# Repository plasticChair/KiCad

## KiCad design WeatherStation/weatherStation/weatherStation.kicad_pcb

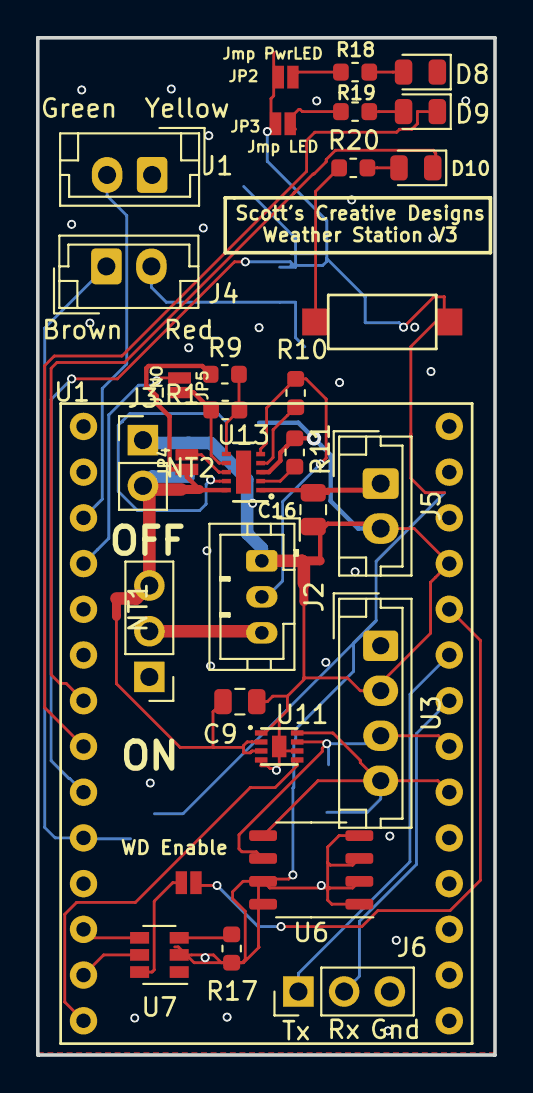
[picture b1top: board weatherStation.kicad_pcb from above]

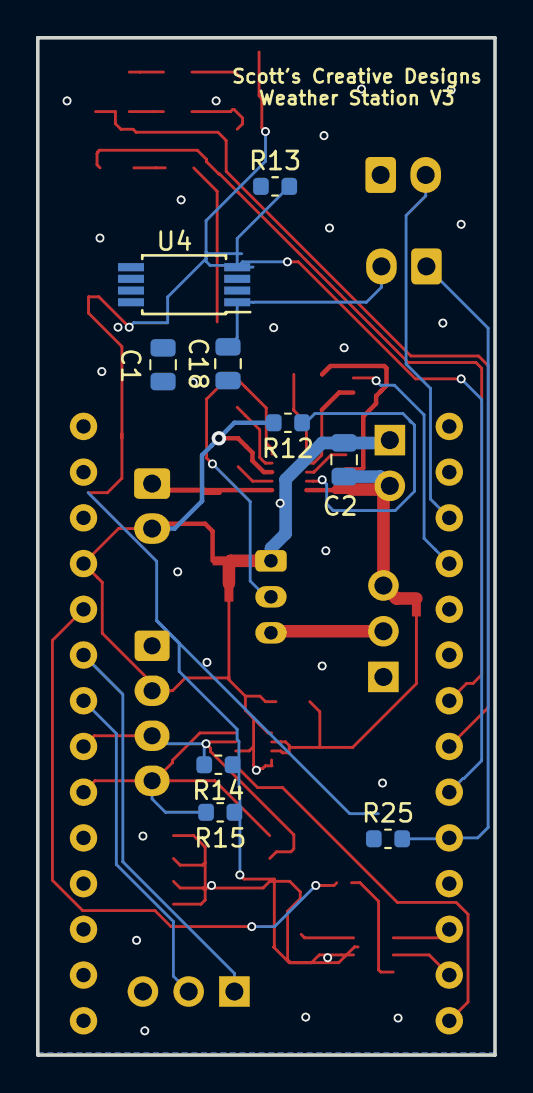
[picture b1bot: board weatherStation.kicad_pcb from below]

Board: 2 copper layers, 25.4 x 56.5 mm, 45 parts (9 on the bottom side), 37 nets.

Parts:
C1, C18: 100nF; C_0805_2012Metric
C2, C16: 1uF; C_0805_2012Metric
C9: 0.1uF; C_0805_2012Metric
D8: 3V3 OK; LED_0805_2012Metric
D9, D10: GPLED; LED_0805_2012Metric
J1, J4, J5: Conn_01x02; JST_EH_B02B-EH-A_1x02_P2.50mm_Vertical
J2: Conn_01x03; JST_PH_B3B-PH-K_1x03_P2.00mm_Vertical
J3: Conn_01x02_Female; PinHeader_1x02_P2.54mm_Vertical
J6: Conn_01x03_Female; PinHeader_1x03_P2.54mm_Vertical
JP1: Jmp_NO; SMT-JUMPER_2_NO_NO-SILK
JP2: Jmp PwrLED; SMT-JUMPER_2_NO_NO-SILK
JP3: Jmp LED; SMT-JUMPER_2_NO_NO-SILK
JP4, JP5: J_NO; SMT-JUMPER_2_NO_NO-SILK
NT1, NT2, NT3, NT4: Net-Tie_2; NetTie-2_SMD_Pad0.5mm
R1, R13, R25: 10k; R_0603_1608Metric
R9: 100k; R_0603_1608Metric
R10: RT; R_0603_1608Metric
R11: 750; R_0603_1608Metric
R12: 330; R_0603_1608Metric
R14, R15: 5k; R_0603_1608Metric
R17: 33k; R_0603_1608Metric
R18, R19, R20: 300; R_0603_1608Metric
SW2: SW_SPDT; PinHeader_1x03_P2.54mm_Vertical
SW3: LED_Push; Tact_SMD_Switch
U1: MKRGSM1400
U3: BME280; JST_EH_B04B-EH-A_1x04_P2.50mm_Vertical
U4: FDW254p; TSSOP-8_4.4x3mm_P0.65mm
U6: MB85RC64; SSOP-8_3.9x5.05mm_P1.27mm
U7: TPL5010; SOT-23-6
U11: MAX17048; TQFN-8_2x2x0.75
U13: BQ24210; WSON-10-1EP_2x3mm_P0.5mm_EP0.84x2.4mm

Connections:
3V3: C1.2, JP2.2, JP3.1, R13.1, R14.1, R15.1, R25.1, SW3.1, U1.26, U3.1, U4.2, U4.3, U6.8, U7.1
/ANE_Pulse: J1.2, U1.3
/ANE_Tx: J4.1, R25.2, U1.10
/ANE_Vcc: C18.2, J4.2, U4.1
/ANE_Vcc_EN: R13.2, U1.9, U4.4
/DONE: U1.12, U7.4
/GPLED1: D9.1, U1.8
/GPLED2: D10.1, U1.7
/RESET: JP1.2, U1.24
/Sheet5C1E5C91/Batt+: C2.1, J3.2, NT1.1, NT2.1, SW2.3
/Sheet5C1E5C91/BattMon+: C9.2, NT1.2, U11.2, U11.3
/Sheet5C1E5C91/Batt_Chrg+: JP4.1, NT2.2, R9.1, U13.10
/Sheet5C1E5C91/Batt_int: J2.3, SW2.2
/Sheet5C1E5C91/NTC: J2.2, R10.2, U13.5
/Sheet5C1E5C91/Solar+: C16.1, J5.1, U13.1
/WAKE: U1.13, U7.5
BATT_ALRT: U1.14, U11.5
CHRG_EN: JP5.1, U1.4
GND: C1.1, C2.2, C9.1, C16.2, C18.1, D8.1, J1.1, J2.1, J3.1, J5.2, J6.3, NT3.1, NT3.2, NT4.1, NT4.2, R11.2, R12.2, R17.1, U1.25, U3.2, U6.1, U6.2, U6.3, U6.4, U6.7, U7.2, U11.1, U11.4, U11.6, U11.9, U13.3
I2C_SCL: R14.2, U1.21, U3.3, U6.6, U11.7
I2C_SDA: R15.2, U1.20, U3.4, U6.5, U11.8
unnamed: D8.2, R18.1
unnamed: D9.2, R19.2
unnamed: D10.2, R20.1
unnamed: J6.1, U1.23
unnamed: J6.2, U1.22
unnamed: JP1.1, U7.6
unnamed: JP2.1, R18.2
unnamed: JP3.2, R19.1
unnamed: JP4.2, U13.8
unnamed: JP5.2, R1.2, U13.7
unnamed: R1.1, R9.2, U13.6
unnamed: R10.1, U13.4
unnamed: R11.1, U13.2
unnamed: R12.1, U13.9
unnamed: R17.2, U7.3
unnamed: R20.2, SW3.2

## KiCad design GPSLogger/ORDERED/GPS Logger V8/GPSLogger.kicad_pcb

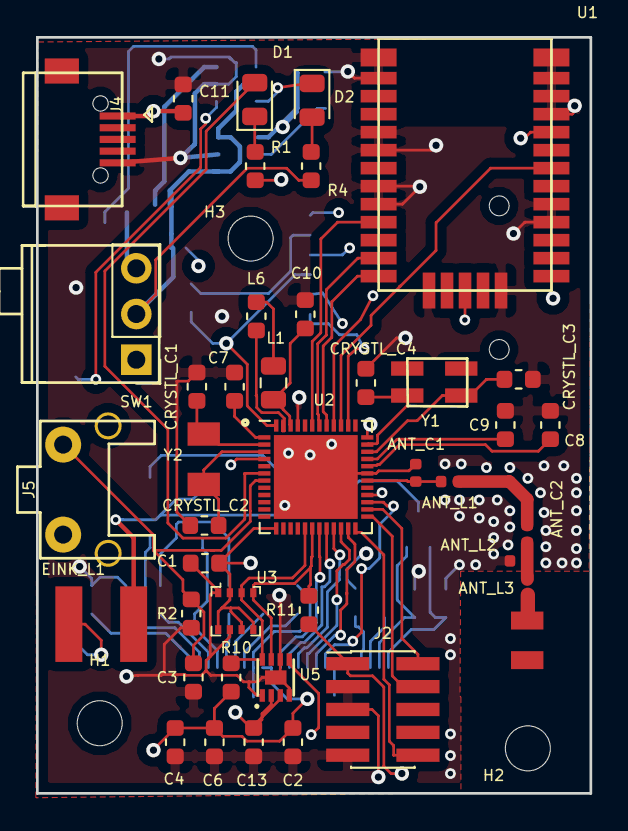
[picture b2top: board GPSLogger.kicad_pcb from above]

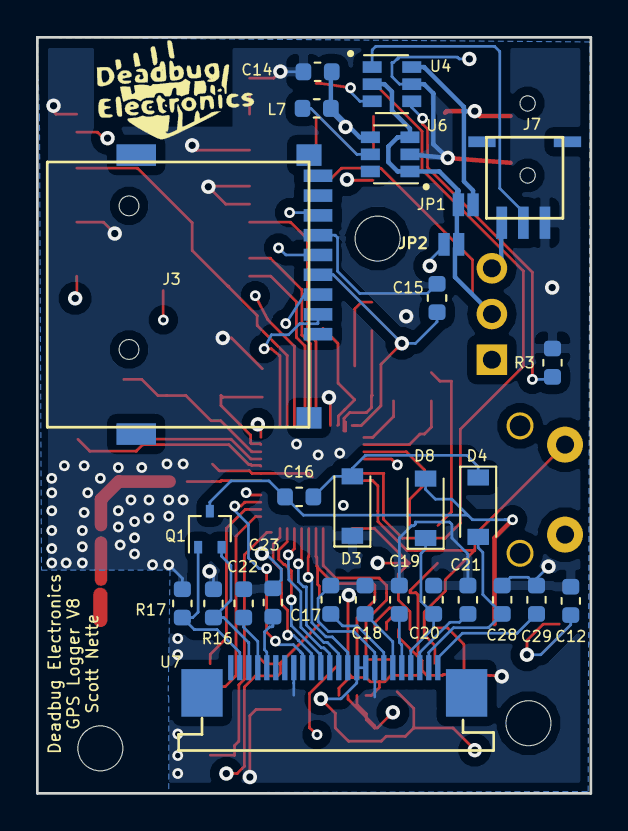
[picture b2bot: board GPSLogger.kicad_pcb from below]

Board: 4 copper layers, 30.8 x 42.0 mm, 72 parts (28 on the bottom side), 61 nets.

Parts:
ANT1: 2450AT18B100E
ANT_C1: 0.8pF; C_0402_1005Metric
ANT_C2: 1.2pF; C_0402_1005Metric
ANT_L1: 3.9nH; L_0402_1005Metric
ANT_L2: 2.7nH; L_0402_1005Metric
ANT_L3: 3.3nH; L_0402_1005Metric
C1: 82n; C_0603_1608Metric
C2: 2.2u; C_0603_1608Metric
C3, C11: 100nF; C_0603_1608Metric
C4, C6: 0.1u; C_0603_1608Metric
C7, C12, C16: 100n; C_0603_1608Metric
C8: NC; C_0603_1608Metric
C9: 100p; C_0603_1608Metric
C10, C13, C17, C18, C19, C20, C21, C22, C23, C28, C29: 1u; C_0603_1608Metric
C14: C; C_0603_1608Metric
C15: 4.7u; C_0603_1608Metric
CRYSTL_C1, CRYSTL_C2, CRYSTL_C3, CRYSTL_C4: 12p; C_0603_1608Metric
D1: LED_B; LED_0805_2012Metric
D2: LED; LED_0805_2012Metric
D3, D4, D8: MBR0530; D_SOD-123
EINK_L1: 68uH; SRN5040TA-680K
H1, H2, H3: MountingHole; MountingHole_2.5mm
J2: Conn_ARM_JTAG_SWD_10; PinHeader_2x05_P1.27mm_Vertical_SMD
J3: Micro_SD_Card; microSD_ebay
J4: USB_B_Micro; USB_Micro-B_Ebay
J5: BTN1; ebay_RA_Mom_switch
J7: Batt_Connector; molex_78172-0003
JP1, JP2: Jumper_NO_Small; SMT-JUMPER_2_NO_NO-SILK
L1: 10nH; L_0805_2012Metric
L6: 15uH; L_0603_1608Metric
L7: INDUCTOR; L_0603_1608Metric
Q1: Q_NMOS_GSD; SOT-323_SC-70
R1: 5.6; R_0603_1608Metric
R2, R17: 10k; R_0603_1608Metric
R3: 1k; R_0603_1608Metric
R4: 330; R_0603_1608Metric
R10, R11: R; R_0603_1608Metric
R16: 0.47; R_0603_1608Metric
SW1: Switch_SW_SPDT; Slide_Switch_RA_09.10290.01
U1: CAM_M8Q; CAM-M8Q
U2: nRF52832-QFxx; QFN-48-1EP_6x6mm_P0.4mm_EP4.66x4.66mm
U3: BME280; Pressure_Sensor_LGA-8_2.5x2.5mm_BME280
U4: BQ21040; SOT-23-6
U5: MAX17048; TQFN-8_2x2x0.75
U6: LM3671; SOT-23-6
U7: 24pin_flex_waveshare; 24pin_Flex_bottom
Y1: 32MHz; ECS-320-12-33Q
Y2: 32.768kHz; TFE322P32K7680R

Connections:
/BatteryManagement/Batt+: JP1.2, JP2.2, R4.1, SW1.2, U4.2, U6.1, U6.3
/BatteryManagement/BattInt: J7.3, SW1.3
/BatteryManagement/NTC: J7.2, U4.1
/DEC1: C7.1, U2.1
/DEC2: C8.1, U2.32
/DEC3: C9.1, U2.33
/DEC4: C10.1, L1.1, U2.46
/EINK/GDR: Q1.1, R17.1, U7.2
/EINK/PREVGH: C20.1, D8.1, U7.21
/EINK/PREVGL: C28.1, D4.2, U7.23
/EINK/RESE: Q1.2, R16.1, U7.3
/EINK/VCOM: C29.1, U7.24
/EINK/VDD: C17.1, U7.18
/EINK/VPP: C18.1, U7.19
/EINK/VSH: C19.1, U7.20
/EINK/VSL: C21.1, U7.22
/EINK_BUSY: U2.27, U7.9
/EINK_DC: U2.22, U7.11
/EINK_RST: U2.23, U7.10
/GPS_ExtInt: U1.7, U2.39
/GPS_Reset: U1.23, U2.43
/GPS_TimePulse: U1.29, U2.40
/RESET: J2.10, U2.24
/SD_CS: J3.2, U2.38
/SPI_CLK: J3.5, U2.20, U7.13
/SPI_EINK_CS: U2.21, U7.12
/SPI_MISO: J3.7, U2.28
/SPI_MOSI: J3.3, U2.19, U7.14
/SWDCLK: J2.4, U2.25
/SWDIO: J2.2, U2.26
ALRT: U2.4, U5.5
BattPwr: C13.1, JP2.1, U5.2, U5.3
BattRtn: ANT_C1.2, ANT_L2.1, C1.2, C2.2, C3.2, C4.1, C6.1, C7.2, C8.2, C9.2, C10.2, C11.1, C12.2, C13.2, C14.2, C15.2, C17.2, C18.2, C19.2, C20.2, C21.2, C22.2, C23.2, C28.2, C29.2, CRYSTL_C1.2, CRYSTL_C2.2, CRYSTL_C3.1, CRYSTL_C4.1, D3.1, J2.3, J2.5, J2.9, J3.6, J4.5, J7.1, R2.2, R3.1, R16.2, R17.2, U1.4, U1.5, U1.10, U1.11, U1.12, U1.13, U1.14, U1.15, U1.18, U1.19, U1.21, U1.22, U1.27, U1.31, U2.31, U2.45, U2.49, U3.1, U3.7, U4.5, U5.1, U5.4, U5.6, U5.9, U6.2, U7.8, U7.17
Fun_Btn_1_P23: C3.1, J5.1, R2.1, U2.7
LED1_P2: D1.2, U2.6
unnamed: ANT1.1, ANT_L3.1
unnamed: ANT_C1.1, ANT_L1.2, U2.30
unnamed: ANT_C2.1, ANT_L1.1
unnamed: ANT_C2.2, ANT_L2.2, ANT_L3.2
unnamed: C16.1, D3.2, D4.1
unnamed: C16.2, D8.2, EINK_L1.2, Q1.3
unnamed: C22.1, U7.4
unnamed: C23.1, U7.5
unnamed: CRYSTL_C1.1, U2.2, Y2.1
unnamed: CRYSTL_C2.1, U2.3, Y2.2
unnamed: CRYSTL_C3.2, U2.34, Y1.1
unnamed: CRYSTL_C4.2, U2.35, Y1.2
unnamed: D1.1, R1.1
unnamed: D2.1, U4.3
unnamed: D2.2, R4.2
unnamed: L1.2, L6.1
unnamed: L6.2, U2.47
unnamed: L7.1, U6.5
unnamed: R3.2, U4.4
unnamed: U1.16, U1.17
SCL: R11.2, U2.18, U3.4, U5.7
SDA: R10.2, U2.17, U3.3, U5.8
UART_RX: U1.25, U2.42
UART_TX: U1.26, U2.41
USB_PWR: C11.2, J4.1, JP1.1, U4.6
Vdd: C1.1, C2.1, C4.2, C6.2, C12.1, C14.1, C15.1, EINK_L1.1, J2.1, J3.4, J5.2, L7.2, R1.2, R10.1, R11.1, U1.1, U1.9, U2.13, U2.36, U2.48, U3.2, U3.5, U3.6, U3.8, U6.4, U7.15, U7.16

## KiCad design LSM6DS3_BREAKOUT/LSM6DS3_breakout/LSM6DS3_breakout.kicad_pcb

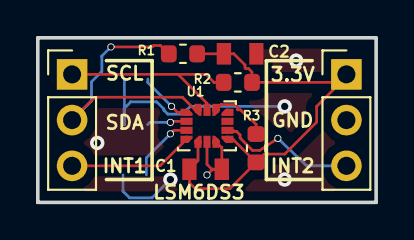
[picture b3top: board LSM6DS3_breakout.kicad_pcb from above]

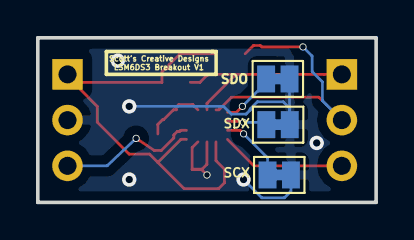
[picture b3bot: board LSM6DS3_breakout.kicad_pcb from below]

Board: 2 copper layers, 18.8 x 9.1 mm, 11 parts (3 on the bottom side), 10 nets.

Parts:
C1, C2: C_Small; 0805
J1, J2: Conn_01x03_Male; PinHeader_1x03_P2.54mm_Vertical
R1, R2: 5.1k; R_0603_1608Metric
R3: 10k; R_0603_1608Metric
SCX: J_NC; SolderJumper-2_P1.3mm_Bridged_Pad1.0x1.5mm
SDO: J_NC; SolderJumper-2_P1.3mm_Bridged_Pad1.0x1.5mm
SDX: J_NC; SolderJumper-2_P1.3mm_Bridged_Pad1.0x1.5mm
U1: LSM6DS3; LGA-14_3x2.5mm_P0.5mm_LayoutBorder3x4y

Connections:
+3V3: C1.2, C2.1, J2.1, R1.2, R2.2, R3.2, U1.5, U1.8
/CS: R3.1, U1.12
/INT1: J1.3, U1.4
/INT2: J2.3, U1.9
/SCL: J1.1, R2.1, U1.13
/SCX: SCX.1, U1.3
/SDA: J1.2, R1.1, U1.14
/SDO: SDO.1, U1.1
/SDX: SDX.1, U1.2
GND: C1.1, C2.2, J2.2, SCX.2, SDO.2, SDX.2, U1.6, U1.7

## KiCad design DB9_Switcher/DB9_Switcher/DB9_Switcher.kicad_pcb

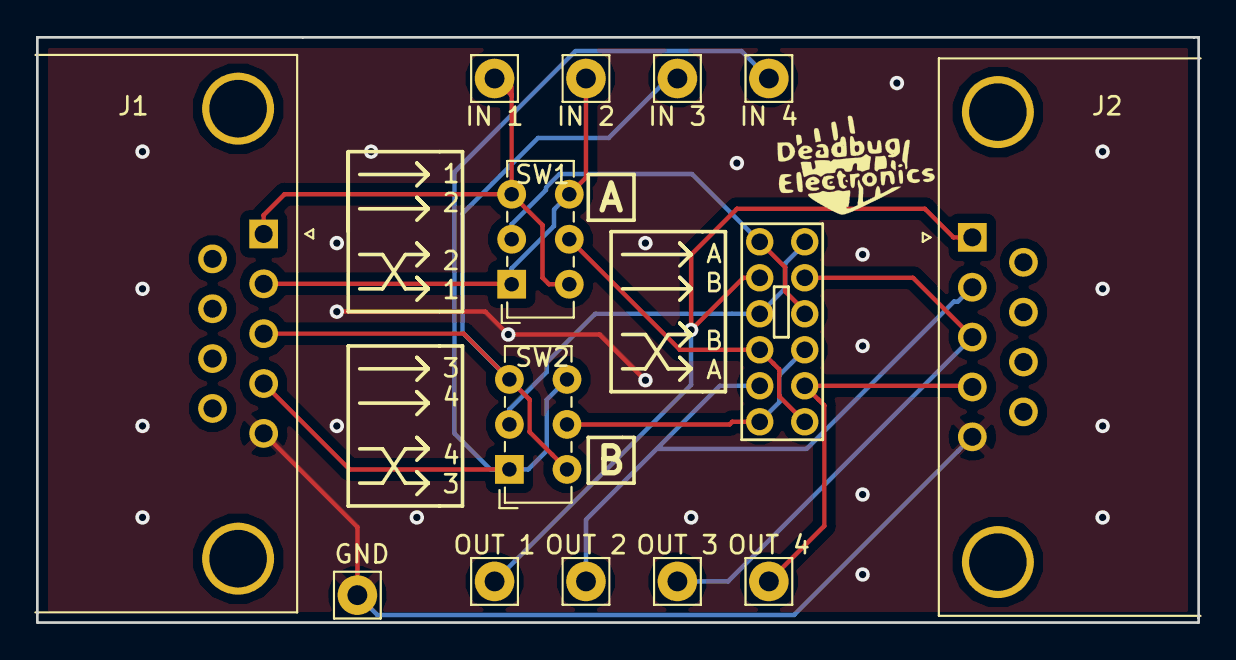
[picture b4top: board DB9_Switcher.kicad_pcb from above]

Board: 2 copper layers, 64.5 x 32.5 mm, 14 parts (0 on the bottom side), 13 nets.

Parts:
GND: GND; Pin_D1.1mm_L8.5mm_W2.5mm_FlatFork
IN 1: IN_1; Pin_D1.1mm_L8.5mm_W2.5mm_FlatFork
IN 2: IN_2; Pin_D1.1mm_L8.5mm_W2.5mm_FlatFork
IN 3: IN_3; Pin_D1.1mm_L8.5mm_W2.5mm_FlatFork
IN 4: IN_4; Pin_D1.1mm_L8.5mm_W2.5mm_FlatFork
J1: DB9_Male; DSUB-9_Male_Horizontal_P2.77x2.84mm_EdgePinOffset9.90mm_Hou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
J2: DB9_Female; DSUB-9_Female_Horizontal_P2.77x2.84mm_EdgePinOffset9.90mm_H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
OUT 1: OUT_1; Pin_D1.1mm_L8.5mm_W2.5mm_FlatFork
OUT 2: OUT_2; Pin_D1.1mm_L8.5mm_W2.5mm_FlatFork
OUT 3: OUT_3; Pin_D1.1mm_L8.5mm_W2.5mm_FlatFork
OUT 4: OUT_4; Pin_D1.1mm_L8.5mm_W2.5mm_FlatFork
SW1, SW2: SW_DPDT_x2; SW_E-Switch_EG1271_DPDT
U1: 4PDTSwitch; MMS42

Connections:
/1: IN 1.1, J1.1, SW1.3, SW1.4
/2: IN 2.1, J1.2, SW1.1, SW1.6
/3: IN 3.1, J1.3, SW2.3, SW2.4
/4: IN 4.1, J1.4, SW2.1, SW2.6
/A_int: SW1.2, U1.1, U1.9
/B_int: SW1.5, U1.4, U1.12
/C_int: SW2.2, U1.3, U1.7
/D_int: SW2.5, U1.6, U1.10
GND: GND.1, J1.5, J2.5
unnamed: J2.1, OUT 1.1, U1.2
unnamed: J2.2, OUT 2.1, U1.5
unnamed: J2.3, OUT 3.1, U1.8
unnamed: J2.4, OUT 4.1, U1.11

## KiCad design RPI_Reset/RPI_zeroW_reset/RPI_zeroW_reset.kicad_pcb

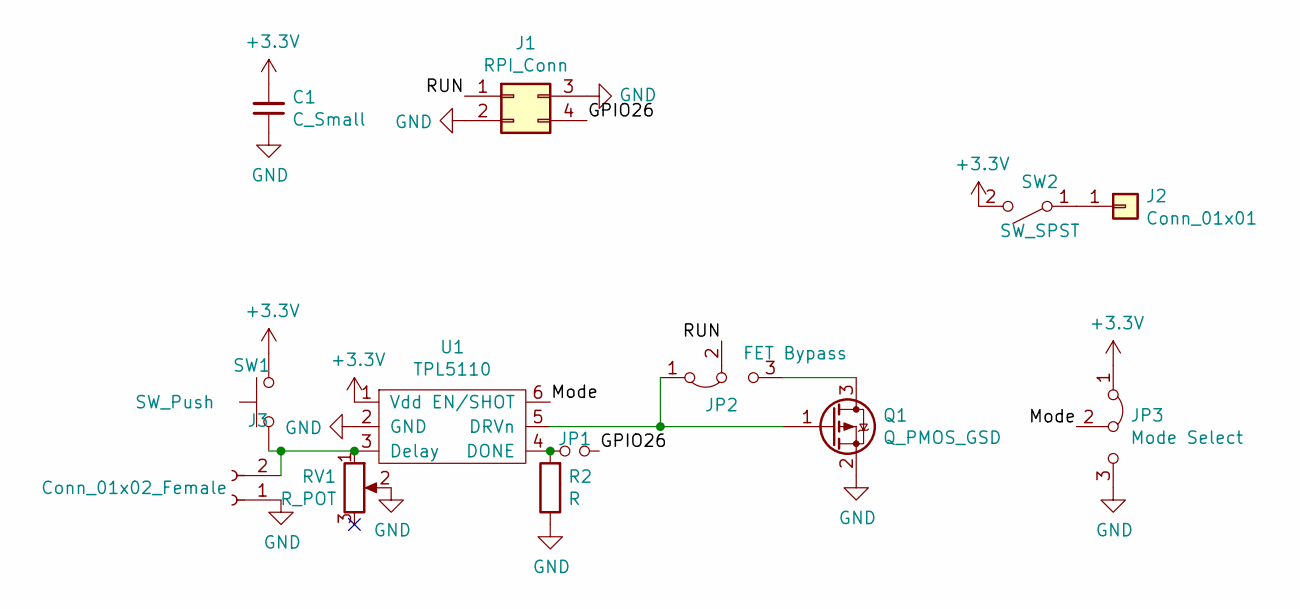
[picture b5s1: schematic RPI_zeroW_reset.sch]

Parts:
C1: C_Small; 0805
J1: RPI_Conn; PinHeader_2x02_P2.54mm_Vertical
J2: Conn_01x01; PinHeader_1x01_P2.54mm_Vertical
J3: Conn_01x02_Female; PinHeader_1x02_P1.27mm_Vertical
JP1: SolderJumper-2_P1.3mm_Open_RoundedPad1.0x1.5mm
JP2: FET Bypass; SolderJumper-3_P1.3mm_Bridged12_RoundedPad1.0x1.5mm
JP3: Mode Select; SolderJumper-3_P1.3mm_Bridged12_RoundedPad1.0x1.5mm
Q1: Q_PMOS_GSD; SOT23
R2: R; R_0805_2012Metric
RV1: R_POT; Bourns_TC33X-2
SW1: SW_Push; Tact_SMD_Switch
SW2: SW_SPST; SWITCH_SPDT_PTH
U1: TPL5110; SOT-23-6

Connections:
+3V3: C1.2, JP3.1 (A), SW1.2, SW2.2 (B), U1.1 (Vdd)
/GPIO26: J1.4, JP1.2
/Mode: JP3.2 (C), U1.6 (EN/SHOT)
/RUN: J1.1, JP2.2 (C)
GND: C1.1, J1.2, J1.3, J3.1, JP3.3 (B), Q1.2 (S), R2.1, RV1.2, U1.2 (GND)
unnamed: J2.1, SW2.1 (A)
unnamed: J3.2, RV1.1, SW1.1, U1.3 (Delay)
unnamed: JP1.1, R2.2, U1.4 (DONE)
unnamed: JP2.1 (A), Q1.1 (G), U1.5 (DRVn)
unnamed: JP2.3 (B), Q1.3 (D)

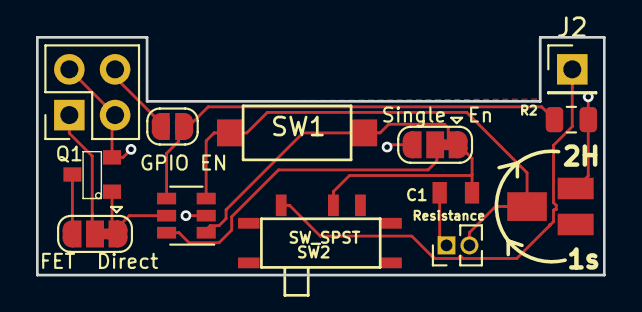
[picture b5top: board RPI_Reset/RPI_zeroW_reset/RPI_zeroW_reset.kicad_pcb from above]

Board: 2 copper layers, 31.5 x 13.2 mm, 13 parts (0 on the bottom side), 10 nets.

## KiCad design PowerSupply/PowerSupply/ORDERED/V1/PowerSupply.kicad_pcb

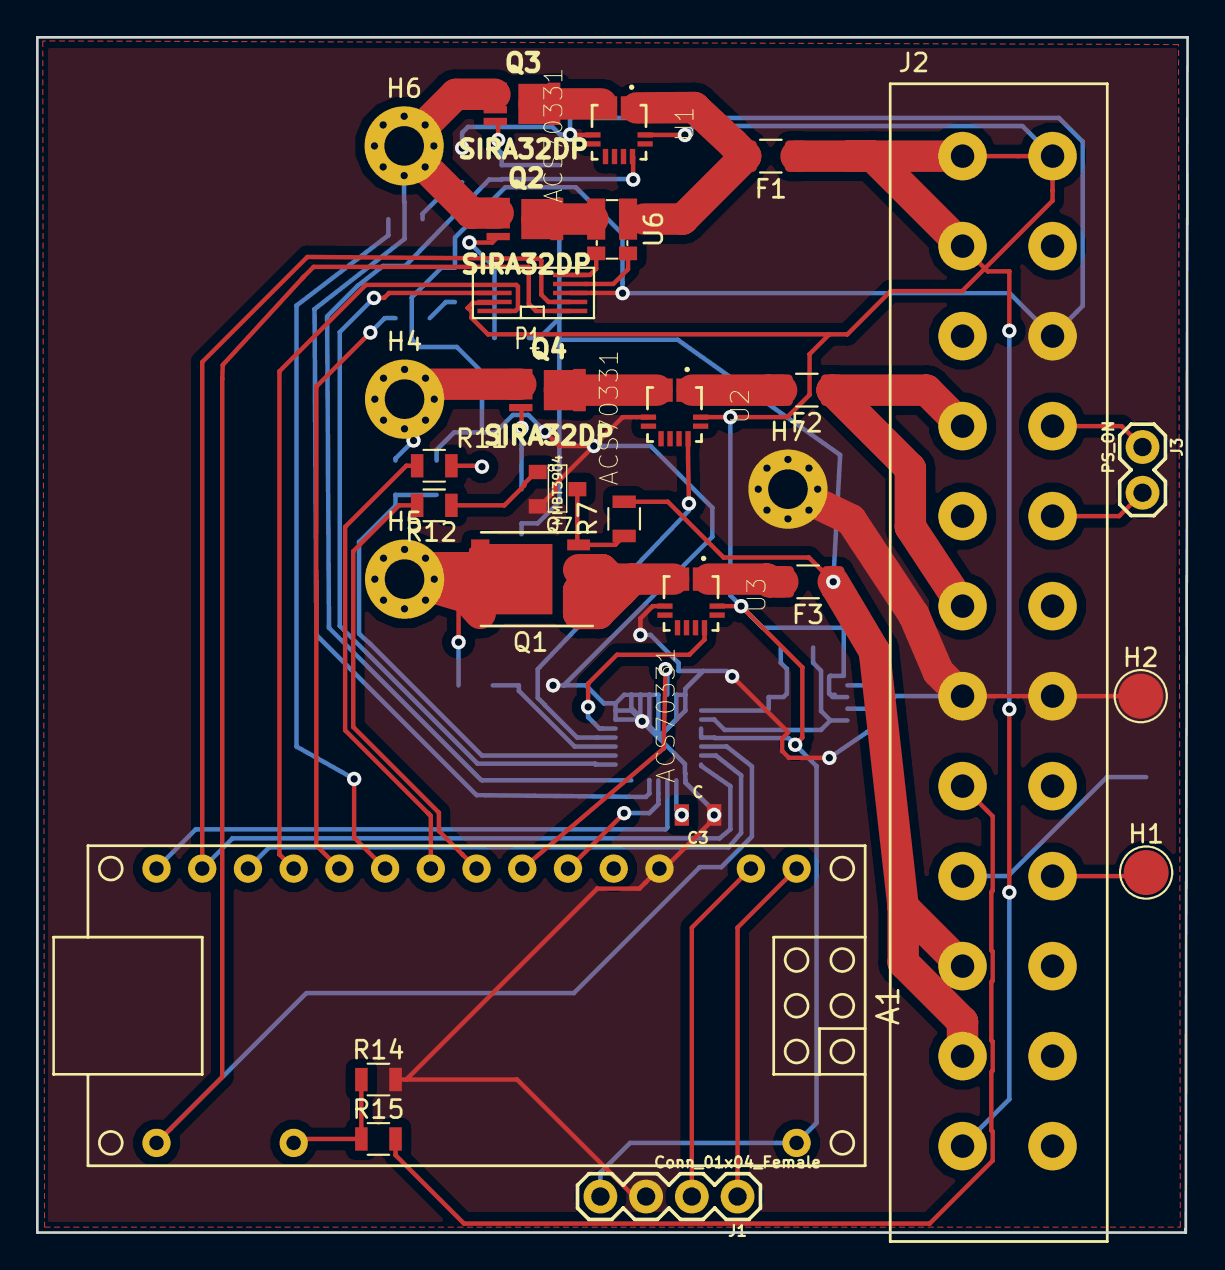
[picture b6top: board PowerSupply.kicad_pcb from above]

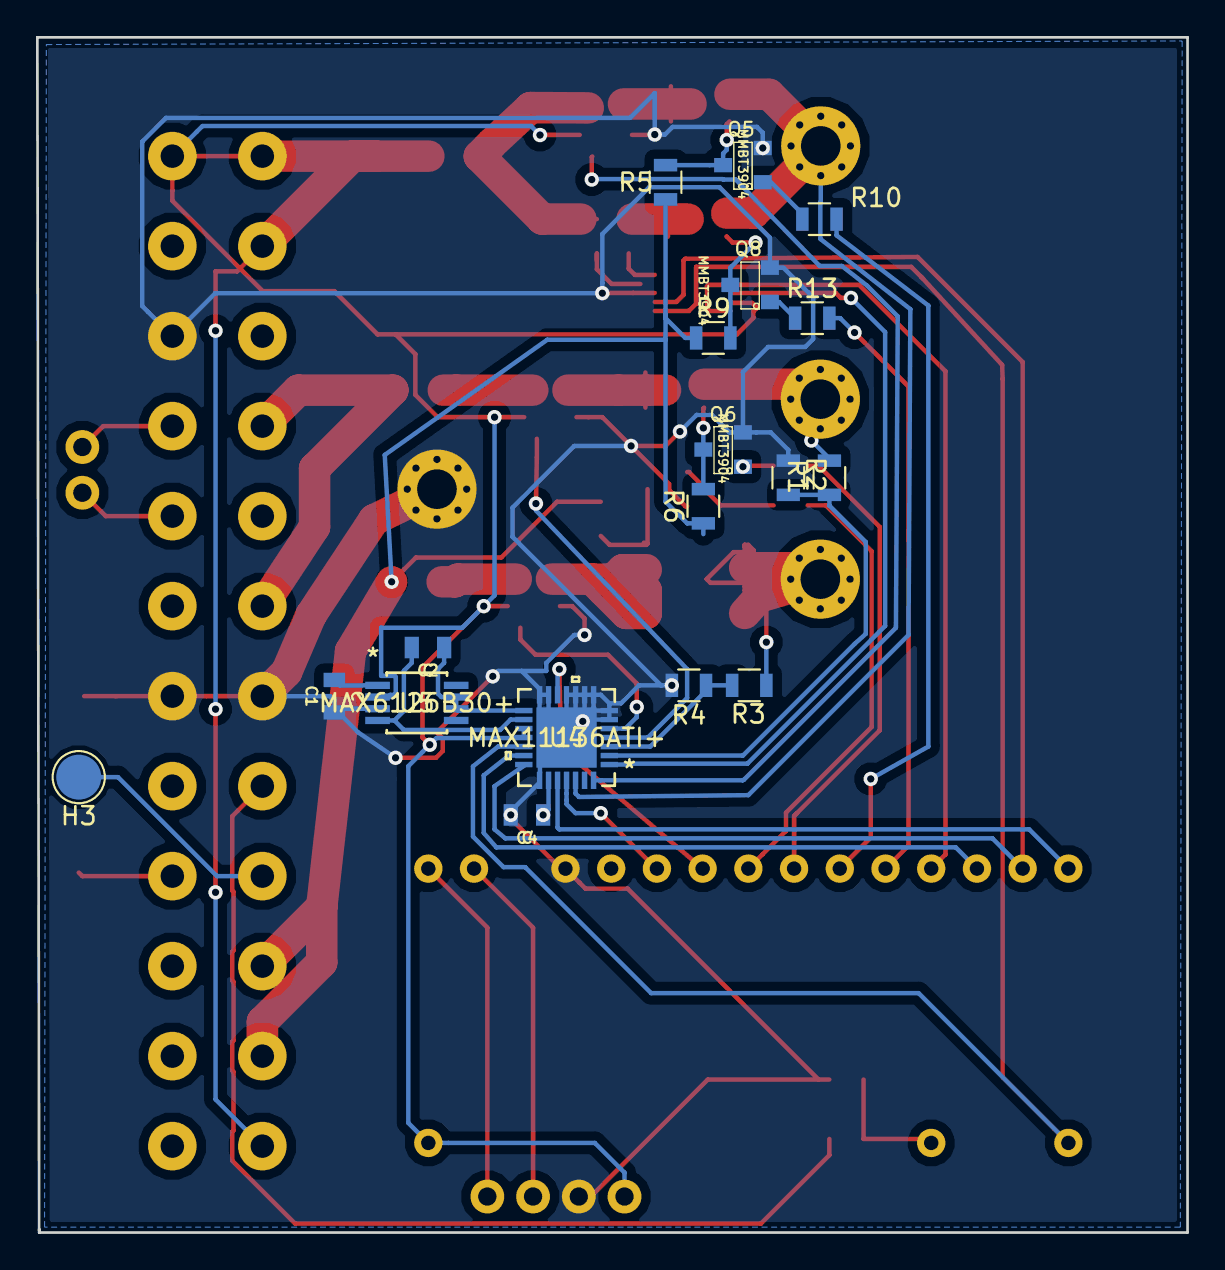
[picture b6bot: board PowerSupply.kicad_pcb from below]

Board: 2 copper layers, 63.9 x 66.4 mm, 47 parts (18 on the bottom side), 53 nets.

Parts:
A1: Arduino_Nano_v3.x; arduino_nano
C1, C2, C3, C4: C; 0805
F1, F2, F3: Polyfuse; Fuse_1206_3216Metric
H1: 5V_load; TestPoint_Pad_D2.5mm
H2: 5V_load_GND; TestPoint_Pad_D2.5mm
H3: 5V_USB; TestPoint_Pad_D2.5mm
H4: 5V_OUT; MountingHole_2.2mm_M2_Pad_Via
H5: 12V_OUT; MountingHole_2.2mm_M2_Pad_Via
H6: 3p3V_OUT; MountingHole_2.2mm_M2_Pad_Via
H7: GND_OUT; MountingHole_2.2mm_M2_Pad_Via
J1: Conn_01x04_Female; 1X04
J2: ATX24; ATX_PWR_25pin
J3: PS_ON; 1X02
P1: MAX9939; uMAX-uSOP_10
Q1: SI7157DP; SO-8_PowerPAK_Vishay_Single
Q2, Q3, Q4: SIRA32DP; PowerPAK-1212-8
Q5, Q6, Q7, Q8: MMBT3904; SOT23
R1, R2, R3, R4, R5, R6, R7, R9: 10k; R_0805
R10, R11, R12, R13: 2.2k; R_0805
R14, R15: R; R_0805
U1, U2, U3: ACS70331; ALLEGRO_ACS70331EESATR-005U3
U4: MAX11136ATI+; MAX11136ATI&plus_
U5: MAX6126B30+; MAX6126B30&plus_
U6: R_0612; R_Shunt_Vishay_WSKW0612

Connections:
3V3_COURSE_EN: A1.10, R10.2
3V3_FINE_EN: A1.11, R13.2
3V3_Fine_Out: P1.8, U4.1
3V3_Out: H6.1, Q2.2, Q3.2, U4.26
5V_DIV_OUT: R1.2, R2.1, U4.2
5V_EN: A1.9, R11.2
5V_Out: H4.1, Q4.2, R1.1
5V_USB: H3.1, J2.9
12V_DIV_Out: R3.2, R4.1, U4.3
12V_EN: A1.8, R12.2
12V_Out: H5.1, Q1.5, R3.1
+3V3: A1.30, F1.1, J1.4, J2.1, J2.2, J2.12, J2.13, P1.9, U1.12, U2.12, U3.12, U4.17, U4.18, U5.2
+12V: F3.1, J2.10, J2.11, R5.1, R6.1, R7.1, R9.1
/3.3VA_D1: Q2.3, U6.4
/3.3VA_D2: Q3.3, U1.3, U1.4
/3.3V_A: F1.2, U1.1, U1.2, U6.1
/5VA: F2.1, J2.4, J2.6
/5VA_D: Q4.3, U2.3, U2.4
/5V_A: F2.2, U2.1, U2.2
/12VA_S: Q1.1, Q1.2, Q1.3, U3.3, U3.4
/12V_A: F3.2, U3.1, U3.2
CNVST_PINX: A1.7, U4.12
EOC_PINX: A1.6, U4.25
GND: A1.4, C1.1, C3.1, C4.1, H2.1, H7.1, J1.3, J2.7, J2.15, J2.19, P1.3, Q5.2, Q6.2, Q7.2, Q8.2, R2.2, R4.2, R14.2, U1.5, U2.5, U3.5, U4.6, U4.7, U4.8, U4.9, U4.10, U4.11, U4.13, U4.14, U4.22, U4.29, U5.3
unnamed: A1.1, J1.1
unnamed: A1.2, J1.2
unnamed: C1.2, U5.1
unnamed: C2.1, U4.16, U5.4
unnamed: C2.2, U4.15, U5.6, U5.7
unnamed: C3.2, C4.2, U4.23
unnamed: H1.1, J2.21
unnamed: J2.8, R15.2
unnamed: J2.16, J3.1
unnamed: J2.17, J3.2
unnamed: P1.4, U6.2
unnamed: P1.5, U6.3
unnamed: Q1.4, Q7.3, R7.2
unnamed: Q2.1, Q8.3, R9.2
unnamed: Q3.1, Q5.3, R5.2
unnamed: Q4.1, Q6.3, R6.2
unnamed: Q5.1, R10.1
unnamed: Q6.1, R11.1
unnamed: Q7.1, R12.1
unnamed: Q8.1, R13.1
unnamed: U1.10, U4.28
unnamed: U2.10, U4.4
unnamed: U3.10, U4.5
POK: A1.19, R14.1, R15.1
SPI_3V3_CS_PINX: A1.12, P1.10
SPI_ADC_CS_PINX: A1.13, U4.20
SPI_Clk_PINX: A1.16, P1.1, U4.19
SPI_MISO_PINX: A1.15, U4.24
SPI_MOSI_PINX: A1.14, P1.2, U4.21

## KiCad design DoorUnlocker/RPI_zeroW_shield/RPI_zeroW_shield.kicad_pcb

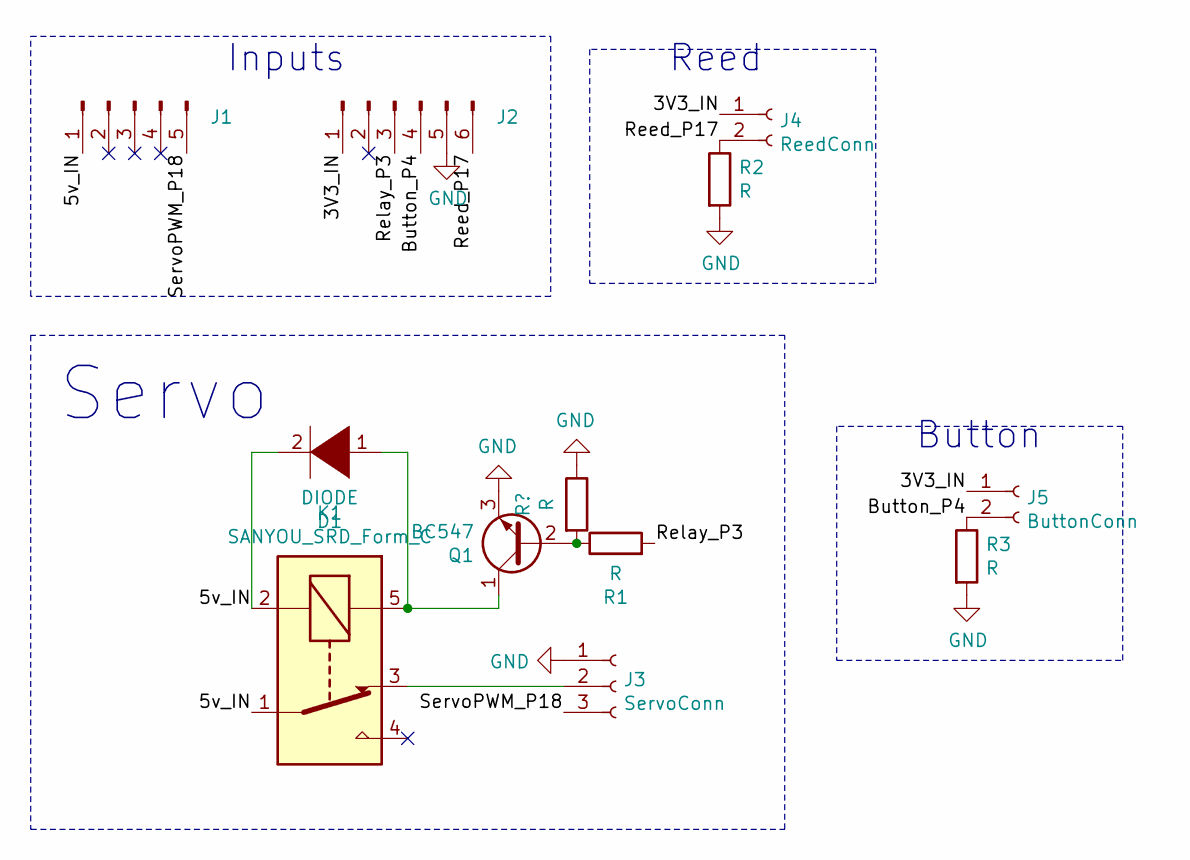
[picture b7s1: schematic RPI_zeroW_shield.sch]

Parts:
D1: DIODE; D_SOD-323_HandSoldering
J1: Conn_01x05_Male; PinHeader_1x05_P2.54mm_Vertical
J2: Conn_01x06_Male; PinHeader_1x06_P2.54mm_Vertical
J3: ServoConn; Pin_Header_1x03_Pitch2.54mm
J4: ReedConn; PinHeader_1x02_P2.54mm_Horizontal
J5: ButtonConn; PinHeader_1x02_P2.54mm_Horizontal
K1: SANYOU_SRD_Form_C; Relay_SPDT_SANYOU_SRD_Series_Form_C
Q1: BC547; TO-92_Inline
R1, R2, R3: R; 1206

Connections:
/3V3_IN: J2.1, J4.1, J5.1
/5v_IN: D1.2 (A), J1.1, K1.1, K1.2
/Button_P4: J2.4, J5.2, R3.1
/Reed_P17: J2.6, J4.2, R2.1
/Relay_P3: J2.3, R1.2
/ServoPWM_P18: J1.5, J3.3
GND: J2.5, J3.1, K1.4, Q1.3 (E), R2.2, R3.2
unnamed: D1.1 (K), K1.5, Q1.1 (C)
unnamed: J3.2, K1.3
unnamed: Q1.2 (B), R1.1

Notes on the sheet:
Servo
Button
Inputs
Reed

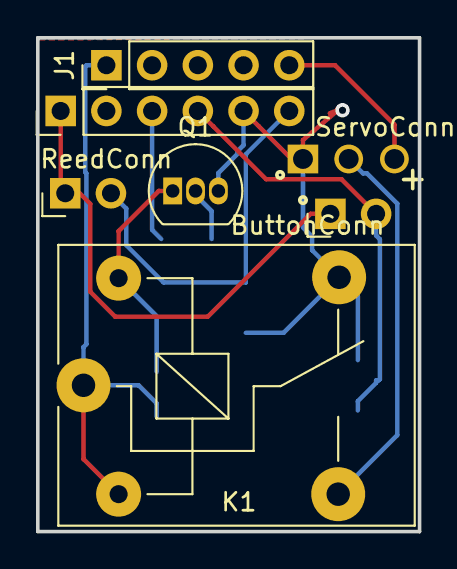
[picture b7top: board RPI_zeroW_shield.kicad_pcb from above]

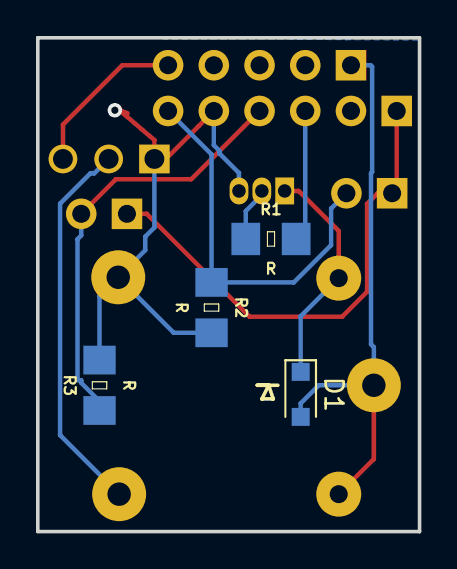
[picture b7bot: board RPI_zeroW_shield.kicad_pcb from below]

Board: 2 copper layers, 21.2 x 27.4 mm, 11 parts (4 on the bottom side), 10 nets.

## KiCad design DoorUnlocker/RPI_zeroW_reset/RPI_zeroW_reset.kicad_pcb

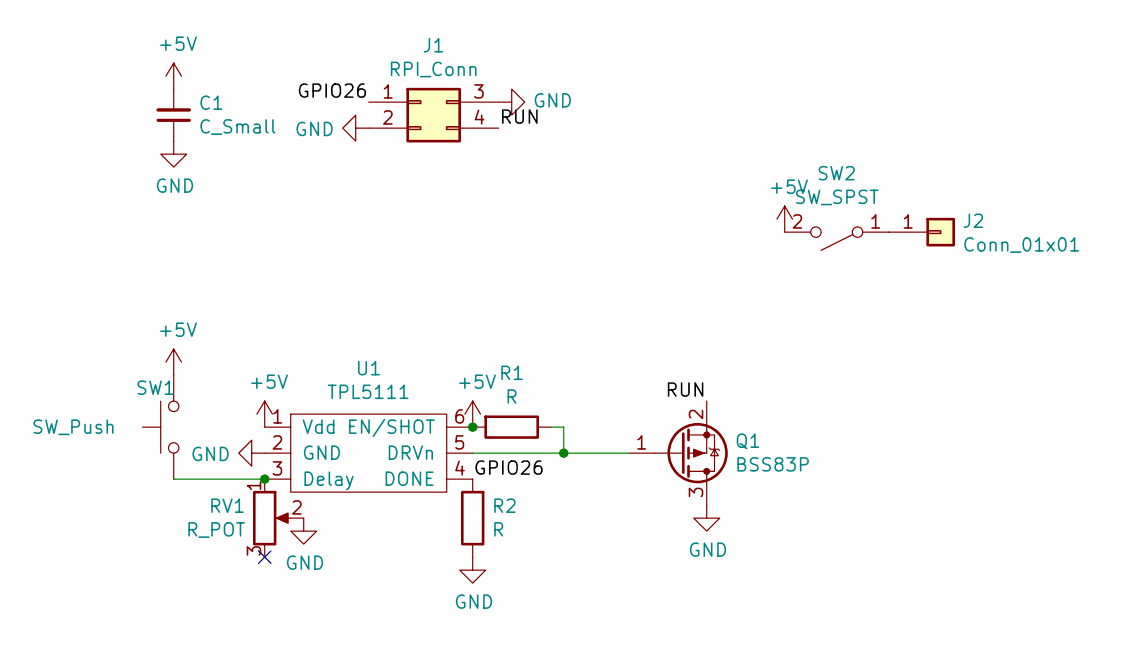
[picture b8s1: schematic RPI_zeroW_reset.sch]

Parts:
C1: C_Small; 0805
J1: RPI_Conn; PinHeader_2x02_P2.54mm_Vertical
J2: Conn_01x01; PinHeader_1x01_P2.54mm_Vertical
Q1: BSS83P; SOT323
R1, R2: R; R_0805_2012Metric
RV1: R_POT; Bourns_TC33X-2
SW1: SW_Push; Tact_SMD_Switch
SW2: SW_SPST; SWITCH_SPDT_PTH
U1: TPL5111; SOT-23-6

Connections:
+5V: C1.2, R1.2, SW1.2, SW2.2 (B), U1.1 (Vdd), U1.6 (EN/SHOT)
/GPIO26: J1.1, R2.2, U1.4 (DONE)
/RUN: J1.4, Q1.2 (S)
GND: C1.1, J1.2, J1.3, Q1.3 (D), R2.1, RV1.2, U1.2 (GND)
unnamed: J2.1, SW2.1 (A)
unnamed: Q1.1 (G), R1.1, U1.5 (DRVn)
unnamed: RV1.1, SW1.1, U1.3 (Delay)

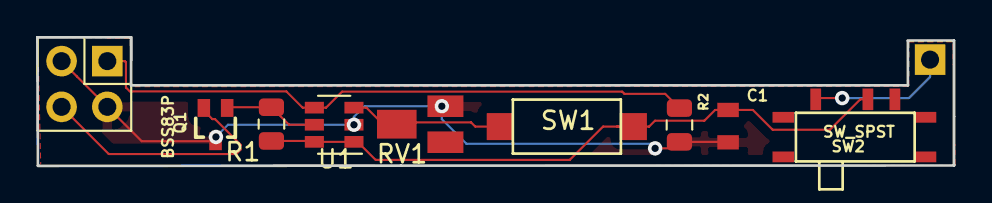
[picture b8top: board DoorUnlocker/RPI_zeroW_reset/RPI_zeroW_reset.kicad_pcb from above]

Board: 2 copper layers, 50.9 x 7.1 mm, 10 parts (1 on the bottom side), 7 nets.

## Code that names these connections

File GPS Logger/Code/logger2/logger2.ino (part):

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Tx = 1  TEENSY2GPS

*/
int SD_CS = 6;
static NMEAGPS  gps;
static gps_fix  fix_data;
int SDLoopCount = 0;
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
  pinMode(13,OUTPUT);
  pinMode(14,OUTPUT);
  //pinMode(SD_CS,OUTPUT);
  //digitalWriteFast(SD_CS,HIGH);
  pinMode(Pin_GPS_pwr,OUTPUT);
  pinMode(Pin_SD_pwr,OUTPUT);
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  adxl.setFreeFallThreshold(255);       // (5 - 9) recommended - 62.5mg per increment
  adxl.setFreeFallDuration(30);       // (20 - 70) recommended - 5ms per increment

  // Setting all interupts to take place on INT1 pin
  //adxl.setImportantInterruptMapping(1, 1, 1, 1, 1);     // Sets "adxl.setEveryInterruptMapping(single tap, double tap, free fall, activity, inactivity);" 
                            // Accepts only 1 or 2 values for pins INT1 and INT2. This chooses the pin on the ADXL345 to use for Interrupts.
                            // This library may have a problem using INT2 pin. Default to INT1 pin.

  // Turn on Interrupts for each mode (1 == ON, 0 == OFF)
  adxl.InactivityINT(0);
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
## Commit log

2018-05-29 Init
2018-10-22 Added Power Supply Project. Need review. custom parts added
2018-10-22 updated. needs updates
2018-10-25 Updated schematic. Need to add to output caps
2018-11-20 Orders from JLCPCB
2018-12-06 pcb updates
2019-01-02 Updated Door Unlocker and PS
2019-01-02 Ordered WeatherStation
2019-06-30 multi project commits
2019-10-07 removed space in folder name. V8 with battery pogo
2019-10-24 commit before more

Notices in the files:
parts and their libraries:
Copyright 2016 Accelerated Designs. All rights reserved.
